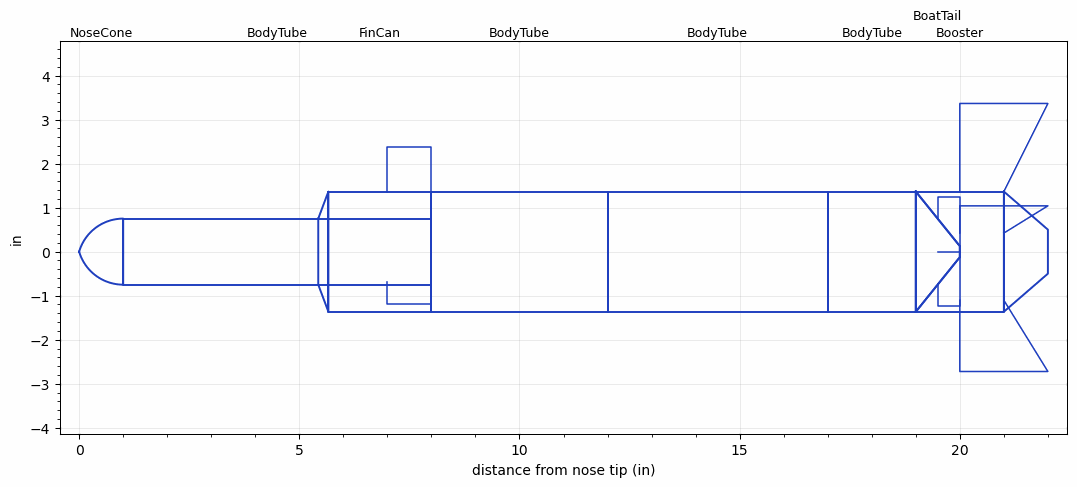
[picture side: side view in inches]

<RASAeroDocument>
 <FileVersion>2</FileVersion>
 <RocketDesign>
  <NoseCone>
   <Length>1</Length>
   <Diameter>1.5</Diameter>
   <Shape>Tangent Ogive</Shape>
   <Location>0</Location>
  </NoseCone>
  <BodyTube>
   <Length>7</Length>
   <Diameter>1.5</Diameter>
   <LaunchLugDiameter>0.2</LaunchLugDiameter>
   <LaunchLugLength>0.4</LaunchLugLength>
   <Location>1</Location>
  </BodyTube>
  <FinCan>
   <Length>2.34</Length>
   <Diameter>2.73</Diameter>
   <InsideDiameter>1.5</InsideDiameter>
   <Location>8</Location>
   <ShoulderLength>0.23</ShoulderLength>
   <Offset>-2.34</Offset>
   <Fin>
    <Count>3</Count>
    <Chord>1</Chord>
    <Span>1</Span>
    <SweepDistance>0</SweepDistance>
    <TipChord>1</TipChord>
    <Thickness>0.5</Thickness>
    <Location>1</Location>
    <AirfoilSection>Single Wedge</AirfoilSection>
   </Fin>
  </FinCan>
  <BodyTube>
   <Length>4</Length>
   <Diameter>2.73</Diameter>
   <RailGuideDiameter>0.25</RailGuideDiameter>
   <RailGuideHeight>0.26</RailGuideHeight>
   <Location>8</Location>
  </BodyTube>
  <BodyTube>
   <Length>5</Length>
   <Diameter>2.73</Diameter>
   <Location>12</Location>
  </BodyTube>
  <BodyTube>
   <Length>2</Length>
   <Diameter>2.73</Diameter>
   <Location>17</Location>
   <BoattailLength>1</BoattailLength>
   <BoattailRearDiameter>0.25</BoattailRearDiameter>
  </BodyTube>
  <BoatTail>
   <Length>1</Length>
   <Diameter>2.73</Diameter>
   <RearDiameter>0.25</RearDiameter>
   <Location>19</Location>
   <Fin>
    <Count>4</Count>
    <Chord>0.5</Chord>
    <Span>0.5</Span>
    <SweepDistance>0</SweepDistance>
    <TipChord>0.5</TipChord>
    <Thickness>0.25</Thickness>
    <Location>0.5</Location>
    <AirfoilSection>Square</AirfoilSection>
   </Fin>
  </BoatTail>
  <Booster>
   <Length>2</Length>
   <Diameter>2.73</Diameter>
   <InsideDiameter>2.73</InsideDiameter>
   <Location>19</Location>
   <ShoulderLength>0</ShoulderLength>
   <BoattailLength>1</BoattailLength>
   <BoattailRearDiameter>1</BoattailRearDiameter>
   <Fin>
    <Count>5</Count>
    <Chord>1</Chord>
    <Span>2</Span>
    <SweepDistance>0</SweepDistance>
    <TipChord>2</TipChord>
    <Thickness>0.25</Thickness>
    <Location>1</Location>
    <AirfoilSection>Rounded</AirfoilSection>
   </Fin>
  </Booster>
  <Surface>Smooth (Zero Roughness)</Surface>
  <ModifiedBarrowman>False</ModifiedBarrowman>
  <Turbulence>False</Turbulence>
  <UseBooster1>False</UseBooster1>
  <UseBooster2>False</UseBooster2>
  <Comments>Comments are for suckers.</Comments>
 </RocketDesign>
 <LaunchSite>
  <Altitude>410</Altitude>
  <Pressure>2</Pressure>
  <RodAngle>20</RodAngle>
  <RodLength>4</RodLength>
  <Temperature>74</Temperature>
  <WindSpeed>1.34</WindSpeed>
 </LaunchSite>
 <Recovery>
  <Altitude1>1000</Altitude1>
  <Altitude2>1000</Altitude2>
  <DeviceType1>Parachute</DeviceType1>
  <DeviceType2>Parachute</DeviceType2>
  <Event1>True</Event1>
  <Event2>True</Event2>
  <Size1>6</Size1>
  <Size2>1</Size2>
  <EventType1>Apogee</EventType1>
  <EventType2>Altitude</EventType2>
  <CD1>1</CD1>
  <CD2>1.33</CD2>
 </Recovery>
 <SimulationList>
  <Simulation>
   <SustainerEngine>1/4A2  (AP)</SustainerEngine>
   <SustainerLaunchWt>1</SustainerLaunchWt>
   <SustainerCG>1</SustainerCG>
   <SustainerIgnitionDelay>0</SustainerIgnitionDelay>
   <Booster1Engine>A8  (ES)</Booster1Engine>
   <Booster1SeparationDelay>0</Booster1SeparationDelay>
   <Booster1IgnitionDelay>0</Booster1IgnitionDelay>
   <IncludeBooster1>True</IncludeBooster1>
   <Booster2Engine>A6Q  (QU)</Booster2Engine>
   <Booster2Delay>0</Booster2Delay>
   <IncludeBooster2>False</IncludeBooster2>
   <TimetoApogee>50.42754</TimetoApogee>
   <MaxAltitude>3.758801</MaxAltitude>
   <MaxVelocity>2.357251</MaxVelocity>
  </Simulation>
  <Simulation>
   <SustainerEngine>C4  (AP)</SustainerEngine>
   <SustainerLaunchWt>1</SustainerLaunchWt>
   <SustainerCG>2</SustainerCG>
   <SustainerIgnitionDelay>0</SustainerIgnitionDelay>
   <Booster1SeparationDelay>0</Booster1SeparationDelay>
   <Booster1IgnitionDelay>0</Booster1IgnitionDelay>
   <IncludeBooster1>False</IncludeBooster1>
   <Booster2Delay>0</Booster2Delay>
   <IncludeBooster2>False</IncludeBooster2>
   <TimetoApogee>1.479999</TimetoApogee>
   <MaxAltitude>10.15928</MaxAltitude>
   <MaxVelocity>29.81428</MaxVelocity>
  </Simulation>
 </SimulationList>
</RASAeroDocument>
